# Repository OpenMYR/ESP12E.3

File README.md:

IoT Motor Hardware: Quad Servo
==============================
by OpenMYR

[OpenMYR Homepage](http://www.OpenMYR.com/)

Software by Brandon Brown and Kyle Berezin

Hardware design by Chris Adams

Hardware licensed under CERN Hardware License Version 1.2

Software licensed under MIT License

This repository is the source files for hardware designed to drive four servo motors with an ESP8266-based platform.

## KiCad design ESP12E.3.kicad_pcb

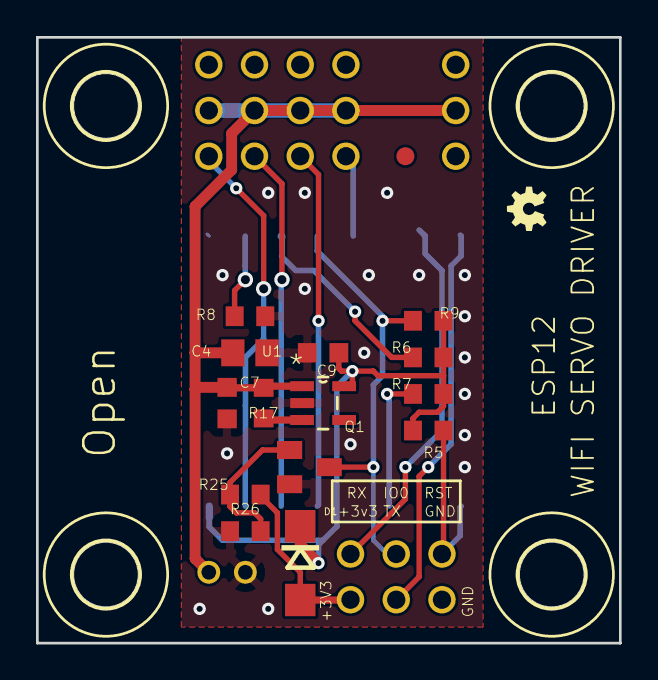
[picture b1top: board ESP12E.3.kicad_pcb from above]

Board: 2 copper layers, 32.4 x 33.7 mm, 30 parts (0 on the bottom side), 11 nets.

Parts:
C3: DNP; E2-4
C4: 4.7uF; C0805
C7, C9: 10uF; C0603K
D1: DIODE-DO214AC; DO214AC
H1, H2, H3, H4: MOUNT-HOLE3.6; 3,6
JP1, JP2, JP3, JP4, JP9, JP10, JP11: PINHD-1X3; 1X03
LOGO1: OSHW-LOGOMINI; OSHW-LOGO-MINI
Q1: MOSFET-NREFLOW; SOT23
R5, R6, R7, R8, R9, R17, R25, R26: 10k; R0603
U1: SPX3819M5-L-3-3; SOT95P280X145-5N
U$3, U$4: FIDUCIAL; FIDUCIAL_1MM
X1: ESP-12

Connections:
+3V3: C9.1, D1.C, R5.2, R6.2, R7.2, R9.2, U1.5, X1.8
/CH_PD: R7.1, X1.3
/GPIO0: Q1.3, R9.1, X1.12
/GPIO2: R6.1, X1.11
/GPIO15: R8.2, X1.10
/P3V3: D1.A, R25.2
/RESET: R5.1, X1.1
GND: C3.-, C4.2, C7.2, C9.2, Q1.2, R8.1, R26.1, U1.2, X1.9
unnamed: Q1.1, R25.1, R26.2
unnamed: R17.1, U1.3
VCC: C3.+, C4.1, C7.1, R17.2, U1.1

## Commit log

2016-04-10 :neckbeard: Added .gitattributes & .gitignore files
2016-04-10 First Commit
    Design 3:
    ESP12E with 4 GPIO driven Servo ports
2016-04-10 New Programming Header
    Modified loading method with 6 pin header.
    Flipped board in layout as most parts were on bottom layer.
    Board power now matches 3 pin servo cable.
2016-07-09 License Update
    Licensed under CERN OHL v.1.2 or later
2018-05-20 //Increased board size and added M3 mounting holes
2018-12-02 Start of ESP12.3 board transfer to KiCAD
2018-12-02 Update to net assignments and part updates.

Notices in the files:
ESP12E.3.kicad_pcb:
Copyright Christopher Adams 2016.
